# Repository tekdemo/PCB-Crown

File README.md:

PCB Crown
=========
A fun experiment in 3D circuits and wearables, designed as a gift to Laen. It was unveiled at the 2014 Maker Faire Bring-a-hack party. 

About The Crown
---------------
The structure of the crown is 11 different panels, held together via PCB Castellations and solder. The 11 panels are made from
5 different designs, and used 3 copies of the tall face plate, and 2 copies of each other design.

The electrical side of the crown is primarily configured to drive 2 individually addressable LED strings. There's a total of 44 RGB LEDs, configured as 2 strings of 22 each
The top uses [8mm Diffused LEDs](https://www.adafruit.com/products/1734), and the faces use [WS2812B SMD LEDs](https://www.adafruit.com/products/1655). These are 
powered by a [SMDuino module](https://code.google.com/p/smduino/), with optional buttons for whatever nefarious purpose seems desirable.

Each module also has a tiny circuit that acts as a SMD equivilent to a breadboard, suitable for future additions of accellerometers, gyros, or light sensors. 
Here's the crown glowing with the full might of the NeoPixels running Adafruit's test patterns. 

WARNING!
--------
This is being published as an demonstration and example project, not as a completed work suitable for replication. 
As an experimental design, this is _highly_ unlikely to work properly for you. The chosen board interconnects are incredibly fragile, and will often stop functioning
if bumped, jostled, or left alone quietly in a dark room. Several part footprints, due to artistic constraints, are maddening to assemble and virtually impossible to test effectively. 
No individual panel will work at all without the adjacent panel, requires at least 1 cut trace, and the LEDs will not work properly without at 
least half the design completed and working. 

Full documentation, build notes, and additional details are posted at [tekdemo.github.io/](https://tekdemo.github.io/pcb-crown/). This includes things not to do, as discovered
in the course of designing and building the crown.

License
--------
Files under `/images/` and the contents of the `gh-pages` branch are liscenced under [Creative Commons Attribution-ShareAlike 4.0](https://creativecommons.org/licenses/by-sa/4.0/)

All other files are released under the [MIT License](http://opensource.org/licenses/MIT).

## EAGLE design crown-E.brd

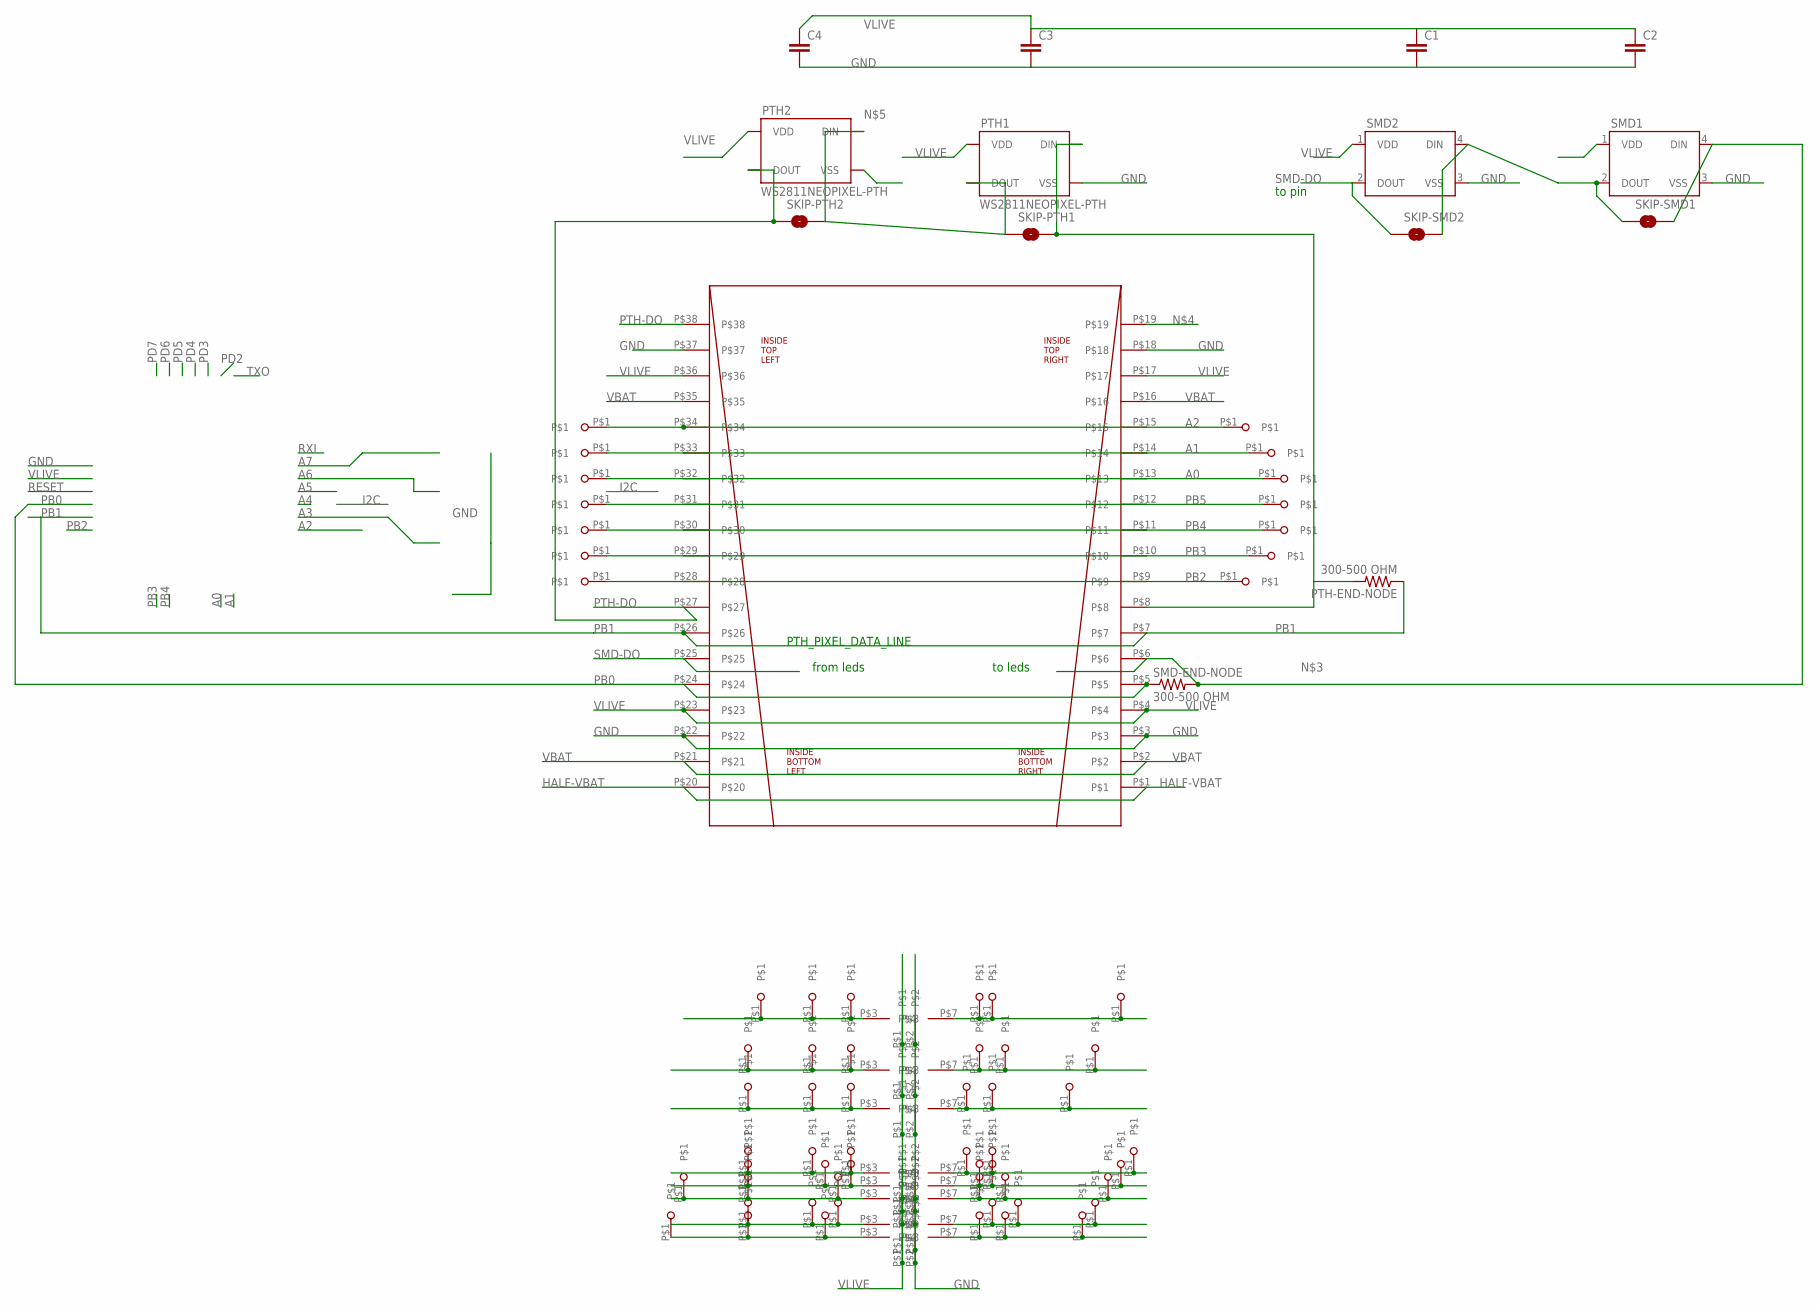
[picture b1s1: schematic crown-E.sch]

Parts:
C1, C2, C3, C4: CAP0805; 0805
PTH1, PTH2: WS2811NEOPIXEL-PTH; WS2811-PTH-FLAT
PTH-END-NODE: 300-500 OHM; 0805
SKIP-PTH1, SKIP-PTH2: SOLDERJUMPERNC2; SJ_2S-NOTRACE
SKIP-SMD1, SKIP-SMD2: SOLDERJUMPERNC2; SJ_2S-NOTRACE
SMD1, SMD2: WS2812B
SMD-END-NODE: 300-500 OHM; 0805
U$1, U$3, U$4, U$5, U$6, U$7, U$8, U$9: SMD_BREADBOARD; SMD_BREADBOARD_4X
U$2: CROWNSTANDARD; CROWN
U$10, U$11, U$12, U$13, U$14, U$15, U$16, U$17, U$18, U$19, U$20, U$21, U$22, U$23, U$24, U$25, U$26, U$27, U$28, U$29, U$30, U$31, U$32, U$33, U$34, U$35, U$36, U$37, U$38, U$39, U$40, U$41, U$42, U$43, U$44, U$45, U$46, U$47, U$48, U$49, U$50, U$51, U$52, U$53, U$54, U$55, U$56, U$57, U$58, U$59, U$60, U$61, U$62, U$63, U$64, U$65, U$66, U$67, U$68, U$69, U$70, U$71: SMD_PAD; SMD_BREADBOARD_PAD

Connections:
A0: U$2.P$13, U$2.P$32, U$44.P$1, U$55.P$1
A1: U$2.P$14, U$2.P$33, U$43.P$1, U$56.P$1
A2: U$2.P$15, U$2.P$34, U$42.P$1, U$58.P$1
GND: C1.2, C2.2, C3.2, C4.2, PTH1.P$2 (VSS), PTH1.P$6 (VSS), PTH2.P$2 (VSS), PTH2.P$6 (VSS), SMD1.3 (VSS), SMD2.3 (VSS), U$1.P$2, U$2.P$3, U$2.P$18, U$2.P$22, U$2.P$37, U$3.P$2, U$4.P$2, U$5.P$2, U$6.P$2, U$7.P$2, U$8.P$2, U$9.P$2
HALF-VBAT: U$2.P$1, U$2.P$20
unnamed: U$1.P$3, U$24.P$1, U$25.P$1, U$63.P$1
unnamed: SKIP-SMD1.2, SMD1.4 (DIN), SMD-END-NODE.2, U$2.P$6
unnamed: PTH1.P$4 (DIN), PTH1.P$8 (DIN), PTH-END-NODE.2, SKIP-PTH1.2, U$2.P$8, U$2.P$19
unnamed: PTH1.P$1 (DOUT), PTH1.P$5 (DOUT), PTH2.P$4 (DIN), PTH2.P$8 (DIN), SKIP-PTH1.1, SKIP-PTH2.2
unnamed: U$3.P$3, U$22.P$1, U$23.P$1, U$62.P$1
unnamed: U$9.P$3, U$20.P$1, U$21.P$1, U$61.P$1
unnamed: U$8.P$3, U$18.P$1, U$19.P$1, U$60.P$1
unnamed: U$4.P$3, U$16.P$1, U$17.P$1, U$59.P$1
unnamed: SKIP-SMD1.1, SKIP-SMD2.2, SMD1.2 (DOUT), SMD2.4 (DIN)
unnamed: U$5.P$3, U$14.P$1, U$15.P$1, U$57.P$1
unnamed: U$6.P$3, U$12.P$1, U$13.P$1, U$50.P$1
unnamed: U$7.P$3, U$10.P$1, U$11.P$1, U$49.P$1
unnamed: U$7.P$7, U$40.P$1, U$41.P$1, U$71.P$1
unnamed: U$6.P$7, U$38.P$1, U$39.P$1, U$70.P$1
unnamed: U$5.P$7, U$36.P$1, U$37.P$1, U$69.P$1
unnamed: U$4.P$7, U$34.P$1, U$35.P$1, U$68.P$1
unnamed: U$8.P$7, U$32.P$1, U$33.P$1, U$67.P$1
unnamed: U$9.P$7, U$30.P$1, U$31.P$1, U$66.P$1
unnamed: U$3.P$7, U$28.P$1, U$29.P$1, U$65.P$1
unnamed: U$1.P$7, U$26.P$1, U$27.P$1, U$64.P$1
PB0: SMD-END-NODE.1, U$2.P$5, U$2.P$24
PB1: PTH-END-NODE.1, U$2.P$7, U$2.P$26
PB2: U$2.P$9, U$2.P$28, U$48.P$1, U$51.P$1
PB3: U$2.P$10, U$2.P$29, U$47.P$1, U$52.P$1
PB4: U$2.P$11, U$2.P$30, U$46.P$1, U$53.P$1
PB5: U$2.P$12, U$2.P$31, U$45.P$1, U$54.P$1
PTH-DO: PTH2.P$1 (DOUT), PTH2.P$5 (DOUT), SKIP-PTH2.1, U$2.P$27, U$2.P$38
SMD-DO: SKIP-SMD2.1, SMD2.2 (DOUT), U$2.P$25
VBAT: U$2.P$2, U$2.P$16, U$2.P$21, U$2.P$35
VLIVE: C1.1, C2.1, C3.1, C4.1, PTH1.P$3 (VDD), PTH1.P$7 (VDD), PTH2.P$3 (VDD), PTH2.P$7 (VDD), SMD1.1 (VDD), SMD2.1 (VDD), U$1.P$1, U$2.P$4, U$2.P$17, U$2.P$23, U$2.P$36, U$3.P$1, U$4.P$1, U$5.P$1, U$6.P$1, U$7.P$1, U$8.P$1, U$9.P$1

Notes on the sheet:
from leds
to pin
to leds
PTH_PIXEL_DATA_LINE

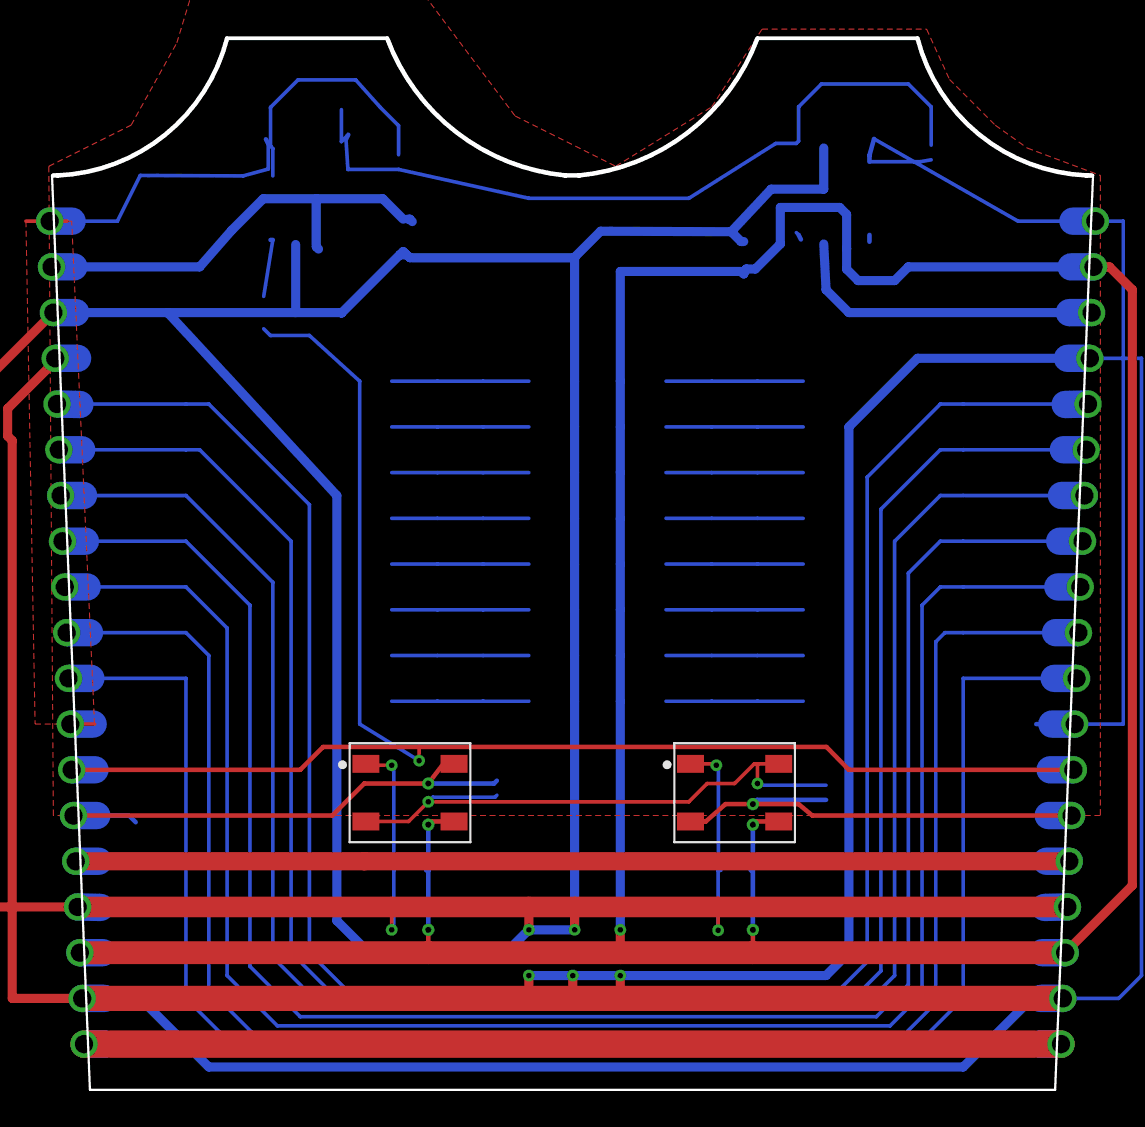
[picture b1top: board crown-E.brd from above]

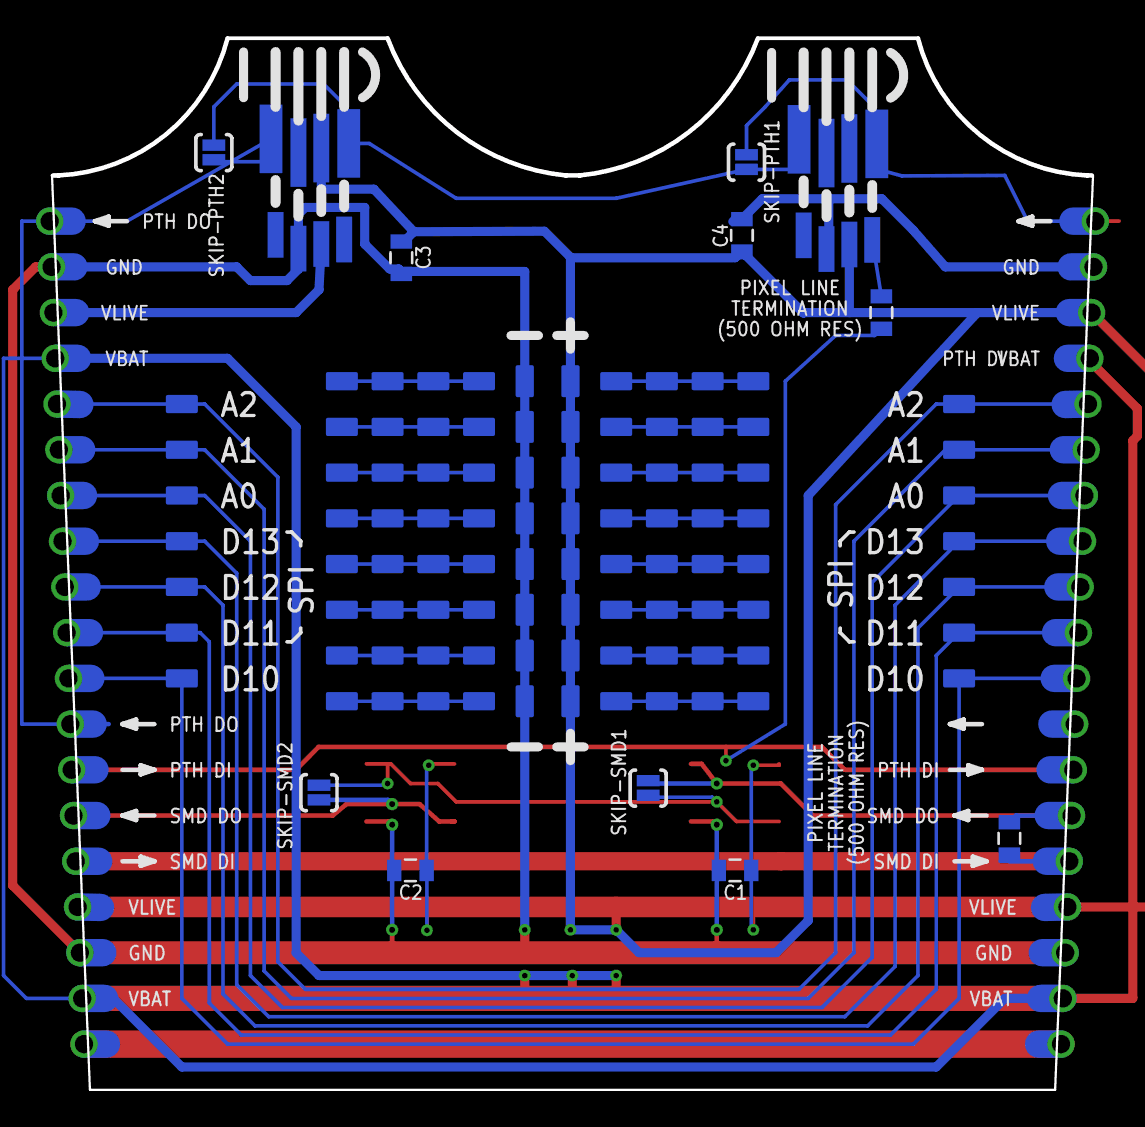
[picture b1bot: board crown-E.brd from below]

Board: 2 copper layers, 57.7 x 58.4 mm, 85 parts (82 on the bottom side), 35 nets.

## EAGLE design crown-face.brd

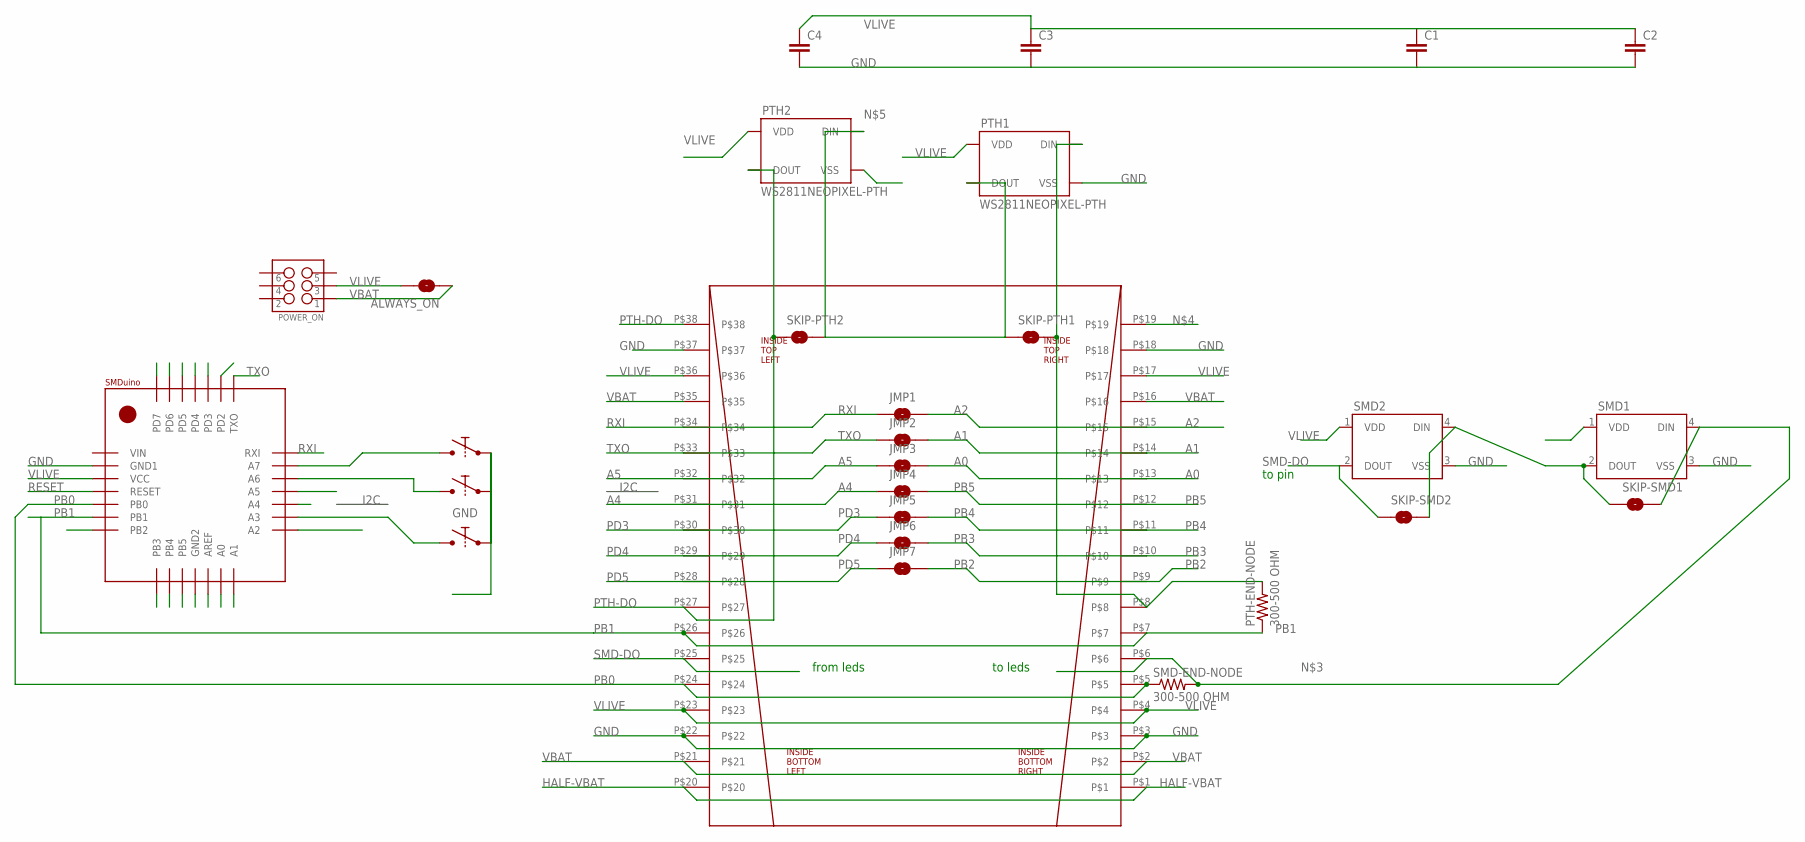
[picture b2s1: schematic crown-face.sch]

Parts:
A6, A7: BUTTONSMD_BUTTON; SMD_BUTTON
ALWAYS_ON: SOLDERJUMPERNC2; SJ_2S-NOTRACE
C1, C2, C3, C4: CAP0805; 0805
D2: BUTTONSMD_BUTTON; SMD_BUTTON
JMP1, JMP2, JMP3, JMP4, JMP5, JMP6, JMP7: SOLDERJUMPERNC2; SJ_2S-NOTRACE
POWER_ON: M03X2FEMALE_SMD; 2X3_SMD
PTH1, PTH2: WS2811NEOPIXEL-PTH; WS2811-PTH-FLAT
PTH-END-NODE: 300-500 OHM; 0805
SKIP-PTH1, SKIP-PTH2: SOLDERJUMPERNC2; SJ_2S-NOTRACE
SKIP-SMD1, SKIP-SMD2: SOLDERJUMPERNC2; SJ_2S-NOTRACE
SMD1, SMD2: WS2812B
SMD-END-NODE: 300-500 OHM; 0805
U$1: SMDUINO
U$2: CROWNSTANDARD; CROWN

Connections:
A0: JMP3.2, U$1.A0, U$2.P$13
A1: JMP2.2, U$1.A1, U$2.P$14
A2: JMP1.2, U$1.A2, U$2.P$15
A3: A6.P$1, A6.P$2, U$1.A3
A4: JMP4.1, U$1.A4, U$2.P$31
A5: JMP3.1, U$1.A5, U$2.P$32
A6: A7.P$1, A7.P$2, U$1.A6
A7: D2.P$1, D2.P$2, U$1.A7
GND: A6.P$3, A6.P$4, A7.P$3, A7.P$4, C1.2, C2.2, C3.2, C4.2, D2.P$3, D2.P$4, PTH1.P$2 (VSS), PTH1.P$6 (VSS), PTH2.P$2 (VSS), PTH2.P$6 (VSS), SMD1.3 (VSS), SMD2.3 (VSS), U$1.GND1, U$2.P$3, U$2.P$18, U$2.P$22, U$2.P$37
HALF-VBAT: U$2.P$1, U$2.P$20
unnamed: SKIP-SMD1.2, SMD1.4 (DIN), SMD-END-NODE.2, U$2.P$6
unnamed: PTH1.P$4 (DIN), PTH1.P$8 (DIN), PTH-END-NODE.2, SKIP-PTH1.2, U$2.P$8, U$2.P$19
unnamed: PTH1.P$1 (DOUT), PTH1.P$5 (DOUT), PTH2.P$4 (DIN), PTH2.P$8 (DIN), SKIP-PTH1.1, SKIP-PTH2.2
unnamed: SKIP-SMD1.1, SKIP-SMD2.2, SMD1.2 (DOUT), SMD2.4 (DIN)
PB0: SMD-END-NODE.1, U$1.PB0, U$2.P$5, U$2.P$24
PB1: PTH-END-NODE.1, U$1.PB1, U$2.P$7, U$2.P$26
PB2: JMP7.2, U$1.PB2, U$2.P$9
PB3: JMP6.2, U$1.PB3, U$2.P$10
PB4: JMP5.2, U$1.PB4, U$2.P$11
PB5: JMP4.2, U$1.PB5, U$2.P$12
PD2: U$1.PD2
PD3: JMP5.1, U$1.PD3, U$2.P$30
PD4: JMP6.1, U$1.PD4, U$2.P$29
PD5: JMP7.1, U$1.PD5, U$2.P$28
PD6: U$1.PD6
PD7: U$1.PD7
PTH-DO: PTH2.P$1 (DOUT), PTH2.P$5 (DOUT), SKIP-PTH2.1, U$2.P$27, U$2.P$38
RESET: U$1.RESET
RXI: JMP1.1, U$1.RXI, U$2.P$34
SMD-DO: SKIP-SMD2.1, SMD2.2 (DOUT), U$2.P$25
TXO: JMP2.1, U$1.TXO, U$2.P$33
VBAT: ALWAYS_ON.1, POWER_ON.1, U$2.P$2, U$2.P$16, U$2.P$21, U$2.P$35
VLIVE: ALWAYS_ON.2, C1.1, C2.1, C3.1, C4.1, POWER_ON.3, PTH1.P$3 (VDD), PTH1.P$7 (VDD), PTH2.P$3 (VDD), PTH2.P$7 (VDD), SMD1.1 (VDD), SMD2.1 (VDD), U$1.VCC, U$2.P$4, U$2.P$17, U$2.P$23, U$2.P$36

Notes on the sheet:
from leds
to pin
to leds

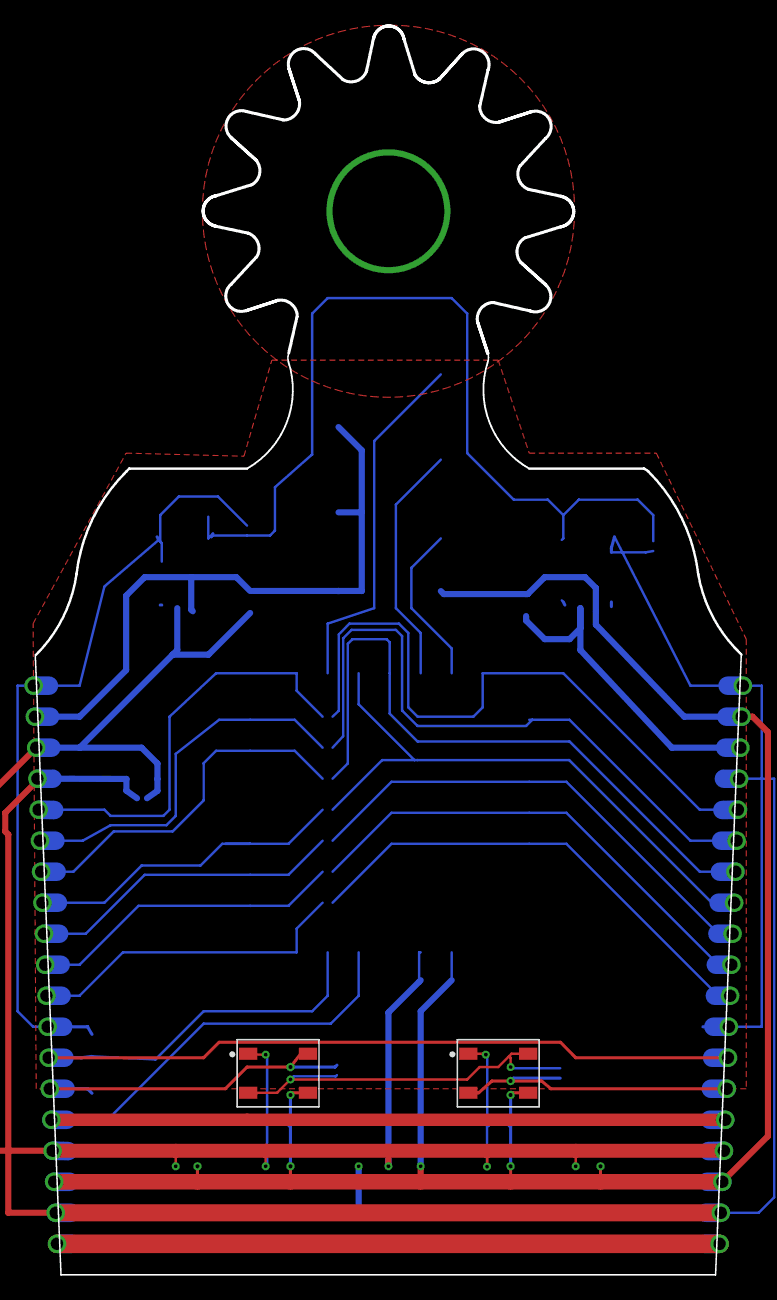
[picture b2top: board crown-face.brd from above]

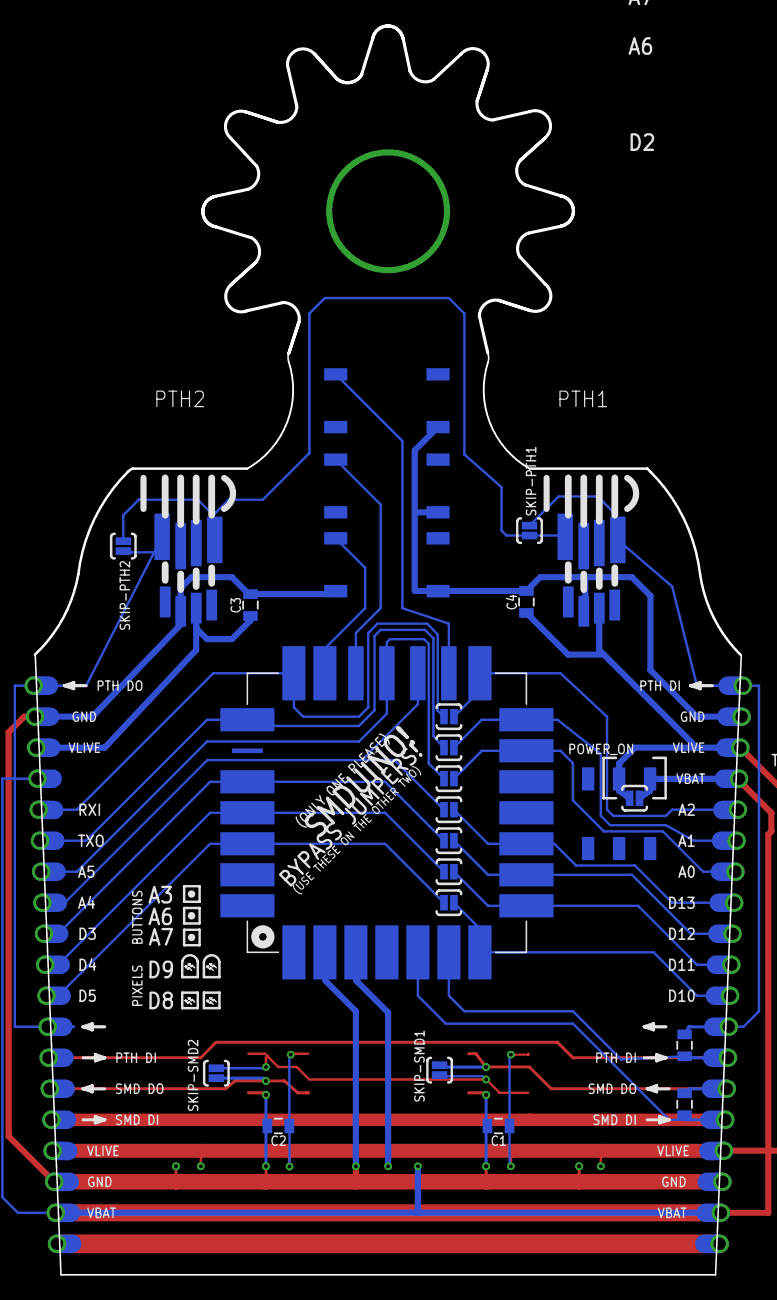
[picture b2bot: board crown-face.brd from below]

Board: 2 copper layers, 57.8 x 102.2 mm, 28 parts (25 on the bottom side), 29 nets.

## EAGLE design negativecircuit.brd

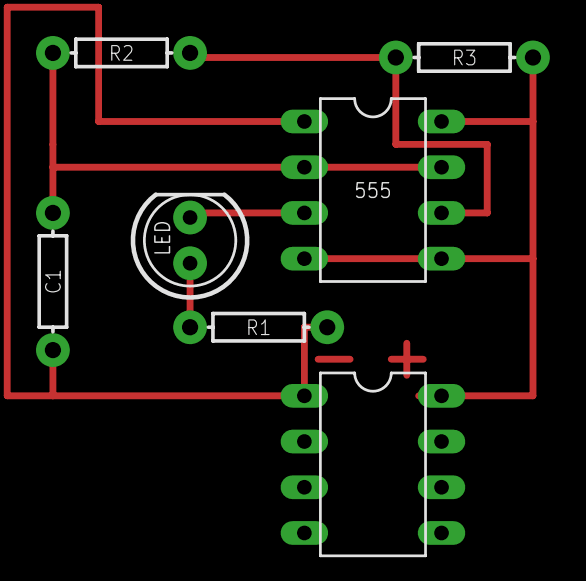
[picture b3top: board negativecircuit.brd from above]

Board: 2 copper layers, 7 parts (0 on the bottom side), 4 nets.

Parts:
555: DIL08
C1: AXIAL-0.3EZ
E$5: DIL08
LED: LED5MM
R1, R2, R3: AXIAL-0.3EZ

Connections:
S$2: 555.3, LED.K
S$4: 555.2, 555.7
S$8: 555.4, 555.5, 555.8
S$9: 555.1, LED.A, R1.P$1, R1.P$2

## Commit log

2014-04-26 Initial commit after completing crown face
2014-04-26 Fixed outline to only show crown
2014-04-26 Made B board, looks a bit funky on the routing.
2014-04-26 Fixed it! :D
2014-04-27 Mostly routed! :D
2014-04-28 Fixed disconnected routes on all panels
    added bypass jumpers across face panel
    added vbat and vlive jumpers from top to bottom
    corrected accidental mirroring
    yay
2014-04-28 Added B plate, which holds battery (best for lipo)
2014-04-28 fixed dimension issue
2014-04-28 Just cleanup stuff
2014-04-28 Added final panel! whooo!
2014-04-28 Fixed top stop layer
2014-04-28 tidied up a little bit
2014-04-28 fixed dimension layer
2014-04-28 Deleted cruft
2014-04-28 Cleanup of stop mask layers
2014-04-28 forgot a connection on skip-smd bits
2014-04-28 fixed incorrect resistor value
2014-04-28 noticed it's WAY THE FUCK WRONG GAAAAH
2014-04-28 Fixed stupid outline mistake on panel E
2014-04-28 forgot the measures
2014-12-23 Prep final project files for publication
2015-02-21 One last update to readme before publishing
2015-02-21 Update Readme
    Always get the image format wrong
2015-02-21 Wrong image link

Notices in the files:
parts and their libraries:
SparkFun-LED: Licensing: Creative Commons ShareAlike 4.0 International - https://creativecommons.org/licenses/by-sa/4.0
